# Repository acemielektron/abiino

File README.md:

# abiino is a arduino compatible diy board which fits into a breadboard

</img>
          
<p>abiino is inspired by <a href="https://www.adafruit.com/product/72">DC Boarduino</a> But unlike DC Boarduino abiino is designed as a single sided pcb for easy toner transfer and etching like most diy boards. </p>
<p>And unlike boarduino abiino has a 3.3v linear voltage regulator on board. Unfortunately on board linear voltage regulator S111733PI is not pin compatible with LM78XX so if you want to use abiino with 5v supply with a 7805 you need to change the layout a bit.
<p>Another difference easily seen is abiino does not have an icsp connector. On a single sided pcb making it is as compact as possible is already  challenge enough and i did not want make it any bulkier. Bootloader can be programmed after putting abiino on a breadboard. </p>
<p>I didn't want to make the board any larger than it already is so a 220 ohm resistor connected top 3.3v power supply is shared between green power led and red led connected to D13 so when red led lights green dims a bit.</p>
<p>An important issue to note is soldering breadboard headers in reverse side -although not impossible- is a bit challenging so if you want to build abiino keep that in mind.
<p>And lastly why abiino, abi (short for agabey) in turkish means elder brother. I designed this board for my little brother so it is abiino.

PCB Layout </img>
Schematic </img>

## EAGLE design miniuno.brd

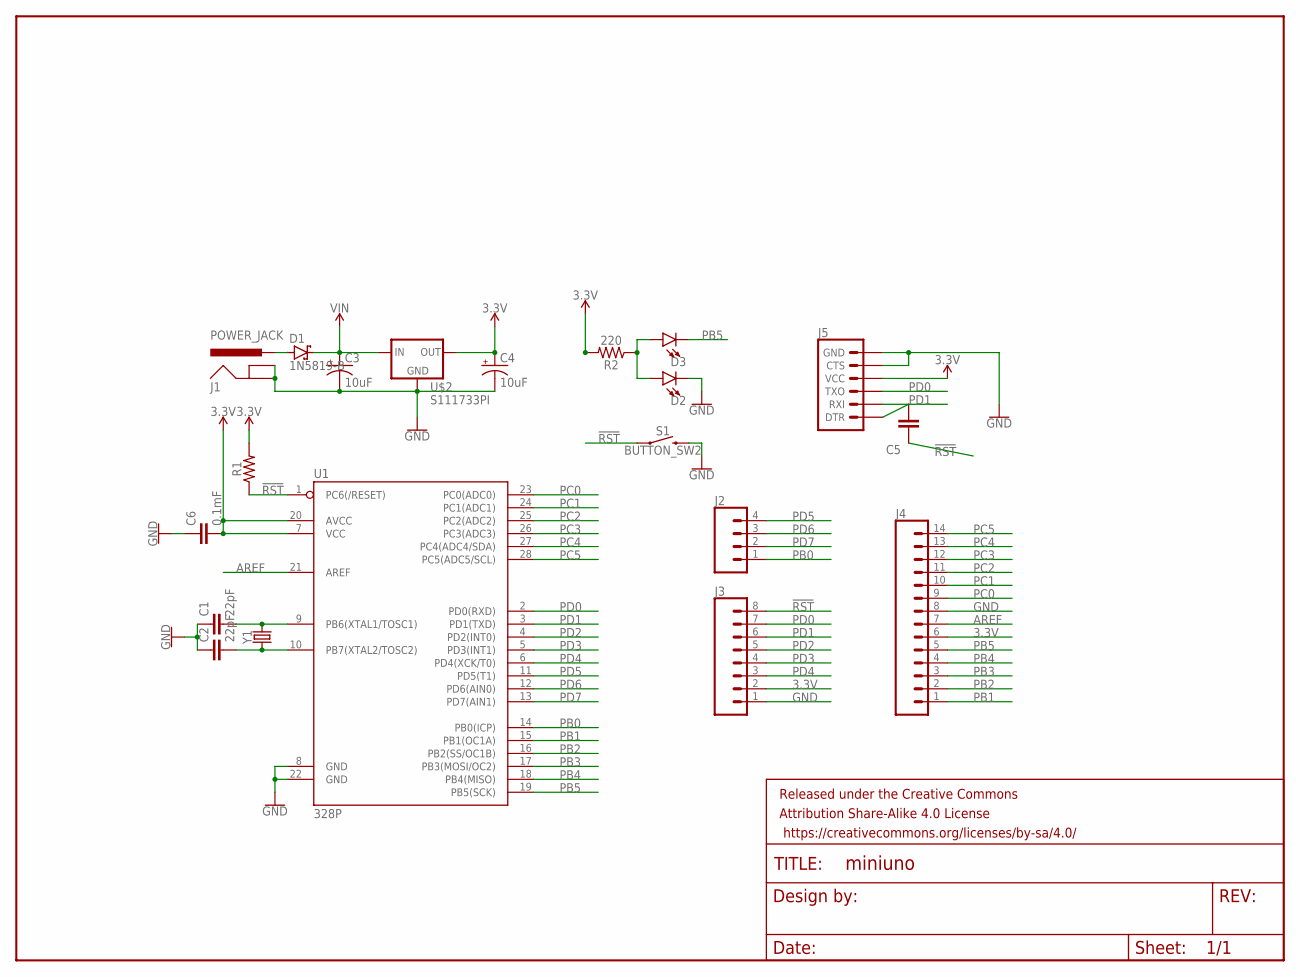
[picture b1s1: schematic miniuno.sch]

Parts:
C1, C2: 22pF; CAP-PTH-2.54
C3, C4: 10uF; CPOL-RADIAL-2.5MM-5MM-KIT
C5: 0.1uF; C5B2.5
C6: 0.1mF; CAP-PTH-2.54
D1: 1N5819-B; DO41-7.6
D2, D3: LED-3MM-NO_SILK; LED_3MM-NS
FRAME1: FRAME-LETTER; CREATIVE_COMMONS
J1: POWER_JACK; POWER_JACK_PTH
J2: CONN_04; 1X04
J3: CONN_08"; 1X08
J4: CONN_14; 1X14
J5: 6_PIN_SERIAL_TARGETPTH-KIT; 1X06-KIT
R1: AXIAL-0.3
R2: 220; AXIAL-0.3
S1: BUTTON_SW2
U1: 328P; DIP28
U$2: S111733PI; S1117XXPI-TO-220
Y1: CRYSTALPTH-HC49US; HC49US

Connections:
3.3V: C4.1 (+), C6.2, J3.2, J4.6, J5.4 (VCC), R1.P$2 (2), R2.P$2 (2), U1.7 (VCC), U1.20 (AVCC), U$2.OUT
!RST: C5.1, J3.8, R1.P$1 (1), S1.1, U1.1 (PC6(/RESET))
AREF: J4.7, U1.21 (AREF)
GND: C1.1, C2.1, C3.2 (-), C4.2 (-), C6.1, D2.K (C), J1.GND, J1.GNDBREAK, J3.1, J4.8, J5.5 (CTS), J5.6 (GND), S1.2, U1.8 (GND), U1.22 (GND), U$2.GND
unnamed: C1.2, U1.9 (PB6(XTAL1/TOSC1)), Y1.2
unnamed: C2.2, U1.10 (PB7(XTAL2/TOSC2)), Y1.1
unnamed: D1.A, J1.PWR
unnamed: C5.2, J5.1 (DTR)
unnamed: D2.A, D3.A, R2.P$1 (1)
PB0: J2.1, U1.14 (PB0(ICP))
PB1: J4.1, U1.15 (PB1(OC1A))
PB2: J4.2, U1.16 (PB2(SS/OC1B))
PB3: J4.3, U1.17 (PB3(MOSI/OC2))
PB4: J4.4, U1.18 (PB4(MISO))
PB5: D3.K (C), J4.5, U1.19 (PB5(SCK))
PC0: J4.9, U1.23 (PC0(ADC0))
PC1: J4.10, U1.24 (PC1(ADC1))
PC2: J4.11, U1.25 (PC2(ADC2))
PC3: J4.12, U1.26 (PC3(ADC3))
PC4: J4.13, U1.27 (PC4(ADC4/SDA))
PC5: J4.14, U1.28 (PC5(ADC5/SCL))
PD0: J3.7, J5.3 (TXO), U1.2 (PD0(RXD))
PD1: J3.6, J5.2 (RXI), U1.3 (PD1(TXD))
PD2: J3.5, U1.4 (PD2(INT0))
PD3: J3.4, U1.5 (PD3(INT1))
PD4: J3.3, U1.6 (PD4(XCK/T0))
PD5: J2.4, U1.11 (PD5(T1))
PD6: J2.3, U1.12 (PD6(AIN0))
PD7: J2.2, U1.13 (PD7(AIN1))
VIN: C3.1 (+), D1.C, U$2.IN

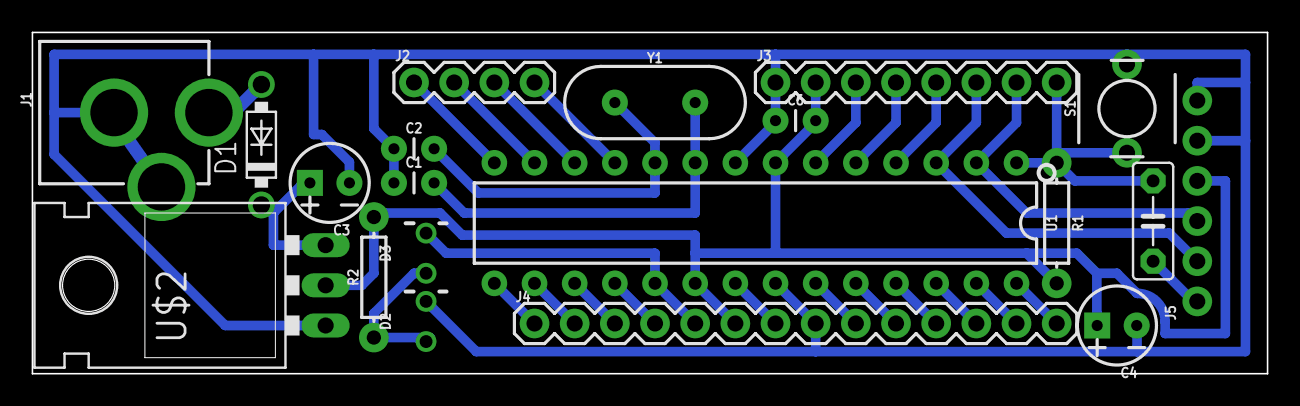
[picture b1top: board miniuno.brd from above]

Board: 2 copper layers, 78.1 x 21.6 mm, 21 parts (0 on the bottom side), 30 nets.

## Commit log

2019-03-31 photos
2019-03-31 board and schematic

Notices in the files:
parts and their libraries:
SparkFun-Capacitors: Licensing: Creative Commons ShareAlike 4.0 International - https://creativecommons.org/licenses/by-sa/4.0
SparkFun-Aesthetics: Released under the Creative Commons Attribution Share-Alike 4.0 License
SparkFun-Aesthetics: https://creativecommons.org/licenses/by-sa/4.0
